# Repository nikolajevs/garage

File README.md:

# 🚨 Garage Alarm System — ESP32 + LD2410C + RC522

Умная охранная сигнализация для гаража на базе ESP32.

## Возможности

- Детекция присутствия человека с помощью радара **LD2410C** (mmWave)
- Управление через RFID-считыватель **RC522** (SPI)
- Задержки на выход (30 сек) и вход (15 сек)
- Фильтр ложных срабатываний: тревога, только если присутствие держится не меньше 1 сек
- Автоматическое отключение сирены через 3 минуты (LED продолжает мигать, пока охрану не снимут картой)
- **Динамическое добавление карт через мастер-карту** — не нужно перепрошивать, чтобы добавить новую карту
- Все карты и мастер-карта хранятся в NVS (переживают перезагрузку и перепрошивку)
- Состояние охраны тоже хранится в NVS — отключение питания не снимает охрану
- Контроль радара: если при охране от LD2410 нет данных дольше 3 сек (обрыв/саботаж), запускается тревога
- Автоматическая переинициализация RC522, если он завис или сбросился от помех

## Пины подключения

| Компонент       | Пин ESP32     |
|-----------------|---------------|
| LD2410C TX      | GPIO16 (RX2)  |
| LD2410C RX      | GPIO17 (TX2)  |
| RC522 SDA (SS)  | GPIO5         |
| RC522 RST       | GPIO4         |
| RC522 SCK       | GPIO18        |
| RC522 MOSI      | GPIO23        |
| RC522 MISO      | GPIO19        |
| RC522 3.3V      | 3.3V (⚠️ не 5V!) |
| Сирена/Реле     | GPIO32        |
| LED индикатор   | GPIO2         |

⚠️ RC522 питается строго от 3.3V — модуль обычно не имеет своего стабилизатора и не 5V-толерантен.
Сирену пришлось перенести с GPIO18 на GPIO32, так как GPIO18 занят аппаратным SPI (SCK) для RC522.

## Как работает

- **DISARMED** — Охрана выключена
- **EXIT_DELAY** — 30 сек на выход (медленное мигание LED)
- **ARMED** — Охрана активна (LED горит)
- **ENTRY_DELAY** — 15 сек на отключение (быстрое мигание)
- **ALARM** — Тревога! Сирена орёт

## Настройка

1. Загрузите прошивку и откройте Serial Monitor (115200 baud).
2. При первом запуске мастер-карта ещё не назначена — поднесите **любую** карту к RC522, она автоматически станет мастер-картой и сохранится в NVS.
3. Чтобы добавить обычную карту: поднесите **мастер-карту** (система должна быть снята с охраны, DISARMED) — LED начнёт часто мигать, это значит включён режим добавления. В течение 15 секунд поднесите новую карту — она сохранится в список разрешённых.
4. Повторное поднесение мастер-карты выключает режим добавления вручную (иначе он сам выключится через 15 сек).
5. Откалибруйте LD2410C через приложение HLKRadarTool.

### Serial-команды

| Команда | Действие |
|---|---|
| `list` | Показать мастер-карту и список обычных карт |
| `clear` | Удалить все обычные карты (мастер-карта не трогается) |
| `resetmaster` | Сбросить мастер-карту — следующая поднесённая карта станет новой мастер-картой |

## Библиотеки

- [MyLD2410](https://github.com/iavorvel/MyLD2410)
- [MFRC522](https://github.com/miguelbalboa/rfid)

**Проект готов к использованию!**

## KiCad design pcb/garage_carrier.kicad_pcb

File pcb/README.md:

# PCB — несущая плата Garage Alarm

Проект KiCad (v7+, открывается и в KiCad 8/9) несущей платы под готовые модули.
Размер платы: **92 × 72 мм**, 2 слоя, 4 монтажных отверстия M3.

## Файлы

- `garage_carrier.kicad_pro` — файл проекта
- `garage_carrier.kicad_sch` — схема (связи заданы глобальными метками)
- `garage_carrier.kicad_pcb` — плата: все посадочные места расставлены, цепи назначены, земляной полигон на нижнем слое (B.Cu)
- `preview.svg` — картинка-превью компоновки
- `generate.py` — скрипт, которым сгенерирован проект (можно менять параметры и перегенерировать)

## Что нужно сделать в KiCad перед заказом

1. Открыть `garage_carrier.kicad_pcb`, нажать **B** — зальётся земляной полигон.
2. **Развести сигнальные дорожки по линиям ratsnest** (~15 цепей). Питание (+12V, +5V) — дорожки 1.0 мм, сигналы — 0.3 мм. Все компоненты выводные, поэтому дорожки можно вести по обоим слоям без переходных отверстий.
3. Запустить DRC, исправить замечания.
4. Экспортировать гербер-файлы скриптом `./export_jlcpcb.sh` (нужен KiCad 7+ в PATH) — он соберёт готовый `garage_carrier_jlcpcb.zip`. Либо вручную: File → Plot (слои F.Cu, B.Cu, F.SilkS, B.SilkS, F.Mask, B.Mask, Edge.Cuts, галка "Subtract soldermask from silkscreen") + Generate Drill Files (Excellon, мм).

## Заказ на JLCPCB

В проект уже прописаны правила под стандартный 2-слойный процесс JLCPCB
(зазор 0.2 мм, дорожка от 0.2 мм, via 0.6/0.3 мм — всё с запасом относительно
их минимумов). Классы цепей: `Default` 0.3 мм для сигналов, `Power` 1.0 мм —
автоматически применяется к +12V, +5V, GND и SIREN_SW.

Параметры при заказе:
- **Layers**: 2, **Thickness**: 1.6 мм
- **Surface Finish**: HASL (with lead) — самый дешёвый, для DIY достаточно
- **Remove Order Number**: "Specify a location" — бесплатно, и номер заказа не окажется посреди шелкографии (добавьте текст `JLCJLCJLCJLC` на F.SilkS в желаемом месте)
- Остальное по умолчанию. 5 плат обычно стоят ~$2-4 + доставка.

PCBA-сборку не закладывал: все компоненты выводные и паяются вручную за вечер,
а THT-сборка на JLC для 5 плат обойдётся дороже самих компонентов.

## Важное допущение

Гнёзда J1A/J1B рассчитаны на **30-контактный ESP32 DevKit (DOIT V1)** с межрядным
расстоянием **25.4 мм**. Если у вас 38-контактный DevKitC — измерьте свою плату и
поправьте координаты в `generate.py` (массив `FP`, строки J1A/J1B), затем перезапустите скрипт.
**Перед заказом обязательно приложите свой DevKit к распечатке платы в масштабе 1:1.**

## Подключение модулей

- **J2 (RC522)** — порядок пинов 1-в-1 как на модуле: SDA, SCK, MOSI, MISO, IRQ, GND, RST, 3.3V → прямой шлейф 8 pin.
- **J3 (LD2410C)** — порядок как на модуле: VCC(5V), GND, OUT, RX, TX.
- **J4** — вход питания 12V DC (клеммник).
- **J5** — сирена 12V: SIREN+ напрямую к +12V, SIREN− коммутируется MOSFET'ом (low-side).
- **J6** — геркон (задел на будущее, GPIO27).
- **U1** — посадочное место под DC-DC модуль 12V→5V (MP1584EN / Mini560). 5V идёт на VIN ESP32 и VCC радара.

## BOM

| Поз. | Компонент | Кол-во |
|---|---|---|
| J1A, J1B | Гнездо PLS 1×15, шаг 2.54 | 2 |
| J2 | Гребёнка/гнездо 1×8 | 1 |
| J3 | Гребёнка/гнездо 1×5 | 1 |
| J4–J6 | Клеммник винтовой 2P, шаг 5.0 | 3 |
| U1 | DC-DC модуль 12V→5V (MP1584EN) | 1 |
| Q1 | IRLZ44N (logic-level N-MOSFET, TO-220) | 1 |
| R1 | 100 Ом 0.25 Вт | 1 |
| R2 | 10 кОм 0.25 Вт | 1 |
| R3 | 330 Ом 0.25 Вт | 1 |
| LED1 | Светодиод 5 мм | 1 |
| D1 | 1N4007 (защитный диод параллельно сирене) | 1 |
| C1 | 470 мкФ 16V электролит (по 5V) | 1 |

## Схема ключа сирены

GPIO32 → R1 (100R) → затвор Q1; R2 (10k) затвор→GND (чтобы сирена молчала при
загрузке ESP32); сток Q1 → SIREN−; исток → GND; D1 катодом к +12V, анодом к
SIREN− — гасит выброс индуктивной нагрузки.

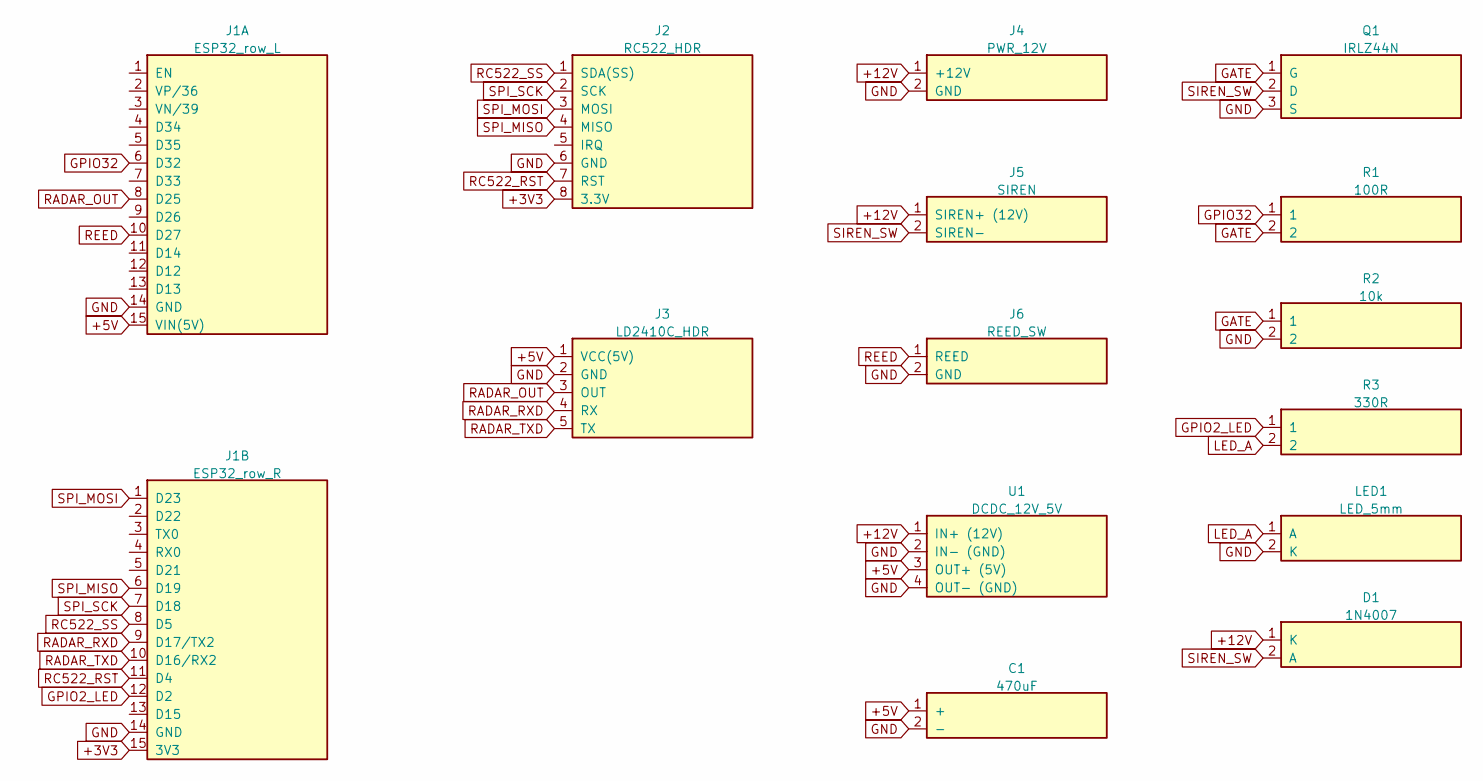
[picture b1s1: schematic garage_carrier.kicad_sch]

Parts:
C1: 470uF; C1
D1: 1N4007; D1
J1A: ESP32_row_L; J1A
J1B: ESP32_row_R; J1B
J2: RC522_HDR; J2
J3: LD2410C_HDR; J3
J4: PWR_12V; J4
J5: SIREN; J5
J6: REED_SW; J6
LED1: LED_5mm; LED1
Q1: IRLZ44N; Q1
R1: 100R; R1
R2: 10k; R2
R3: 330R; R3
U1: DCDC_12V_5V; U1

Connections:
+3V3: J1B.15 (3V3), J2.8 (3.3V)
+5V: C1.1 (+), J1A.15 (VIN(5V)), J3.1 (VCC(5V)), U1.3 (OUT+ (5V))
+12V: D1.1 (K), J4.1 (+12V), J5.1 (SIREN+ (12V)), U1.1 (IN+ (12V))
GATE: Q1.1 (G), R1.2, R2.1
GND: C1.2 (-), J1A.14 (GND), J1B.14 (GND), J2.6 (GND), J3.2 (GND), J4.2 (GND), J6.2 (GND), LED1.2 (K), Q1.3 (S), R2.2, U1.2 (IN- (GND)), U1.4 (OUT- (GND))
GPIO2_LED: J1B.12 (D2), R3.1
GPIO32: J1A.6 (D32), R1.1
LED_A: LED1.1 (A), R3.2
RADAR_OUT: J1A.8 (D25), J3.3 (OUT)
RADAR_RXD: J1B.9 (D17/TX2), J3.4 (RX)
RADAR_TXD: J1B.10 (D16/RX2), J3.5 (TX)
RC522_RST: J1B.11 (D4), J2.7 (RST)
RC522_SS: J1B.8 (D5), J2.1 (SDA(SS))
REED: J1A.10 (D27), J6.1 (REED)
SIREN_SW: D1.2 (A), J5.2 (SIREN-), Q1.2 (D)
SPI_MISO: J1B.6 (D19), J2.4 (MISO)
SPI_MOSI: J1B.1 (D23), J2.3 (MOSI)
SPI_SCK: J1B.7 (D18), J2.2 (SCK)

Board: 2 copper layers, 19 parts (0 on the bottom side), 18 nets, no tracks yet.

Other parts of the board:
H1: M3; H1
H2: M3; H2
H3: M3; H3
H4: M3; H4

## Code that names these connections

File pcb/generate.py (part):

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# ---------------- nets ----------------
NETS = ["", "GND", "+12V", "+5V", "+3V3", "SPI_MOSI", "SPI_MISO", "SPI_SCK",
        "RC522_SS", "RC522_RST", "RADAR_TXD", "RADAR_RXD", "RADAR_OUT",
        "SIREN_SW", "GPIO32", "GATE", "REED", "GPIO2_LED", "LED_A"]
NID = {n: i for i, n in enumerate(NETS)}

# ---------------- components ----------------
# Each: ref, value, list of (padname, pinlabel, net or None), footprint geometry
ESP_L = [("1","EN",None),("2","VP/36",None),("3","VN/39",None),("4","D34",None),
         ("5","D35",None),("6","D32","GPIO32"),("7","D33",None),("8","D25","RADAR_OUT"),
         ("9","D26",None),("10","D27","REED"),("11","D14",None),("12","D12",None),
         ("13","D13",None),("14","GND","GND"),("15","VIN(5V)","+5V")]
ESP_R = [("1","D23","SPI_MOSI"),("2","D22",None),("3","TX0",None),("4","RX0",None),
         ("5","D21",None),("6","D19","SPI_MISO"),("7","D18","SPI_SCK"),("8","D5","RC522_SS"),
         ("9","D17/TX2","RADAR_RXD"),("10","D16/RX2","RADAR_TXD"),("11","D4","RC522_RST"),
         ("12","D2","GPIO2_LED"),("13","D15",None),("14","GND","GND"),("15","3V3","+3V3")]
RC522 = [("1","SDA(SS)","RC522_SS"),("2","SCK","SPI_SCK"),("3","MOSI","SPI_MOSI"),
         ("4","MISO","SPI_MISO"),("5","IRQ",None),("6","GND","GND"),
         ("7","RST","RC522_RST"),("8","3.3V","+3V3")]
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REED = [("1","REED","REED"),("2","GND","GND")]
BUCK = [("1","IN+ (12V)","+12V"),("2","IN- (GND)","GND"),("3","OUT+ (5V)","+5V"),("4","OUT- (GND)","GND")]
Q1   = [("1","G","GATE"),("2","D","SIREN_SW"),("3","S","GND")]
R1   = [("1","1","GPIO32"),("2","2","GATE")]
R2   = [("1","1","GATE"),("2","2","GND")]
R3   = [("1","1","GPIO2_LED"),("2","2","LED_A")]
LED1 = [("1","A","LED_A"),("2","K","GND")]
D1   = [("1","K","+12V"),("2","A","SIREN_SW")]
C1   = [("1","+","+5V"),("2","-","GND")]
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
